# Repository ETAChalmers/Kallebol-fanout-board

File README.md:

# Kallebol-fanout-board
PCB to fan out and io expand the computers GPIO for the rotating Kallebol assembly

The GPIO of the kallebol computer was to slow for I2C. This board did not work and was replaced with a Raspberry Pi Pico instead.  

Features: 

* ~~UART for elevation control~~
* ~~I2C bus~~
* ~~I2C temp sensor~~
* ~~I2C 16 bit IO expander~~
* ~~Coax switch control~~
* ~~2x 12V outputs to drive LNB + 1.3 GHz LNA block.~~
* ~~PTT input to computer ... for future TX use.~~
* ~~12V -> 5V linear regulator, don't use this to power anything power hungry.~~
* ~~5V -> 3.3V linear regulator, don't use this to power anything power hungry.~~
* ~~2x Female RS232 ports (might need to be male in rev 2 ...)~~
* ~~Way too many resistors, all should not be mounted.~~
* ~~Way too many screw terminals~~
* ~~Chinesium (TM) voltmeter to monitor incoming 12V.~~

DC load: 
* Computer, 12V 5A peak 
* 10.5 GHz LNB, 12V ?A
* 1.3 GHz LNA, 12V ?A

Board2Pdf & jlcpcb plugin used in KiCad project.

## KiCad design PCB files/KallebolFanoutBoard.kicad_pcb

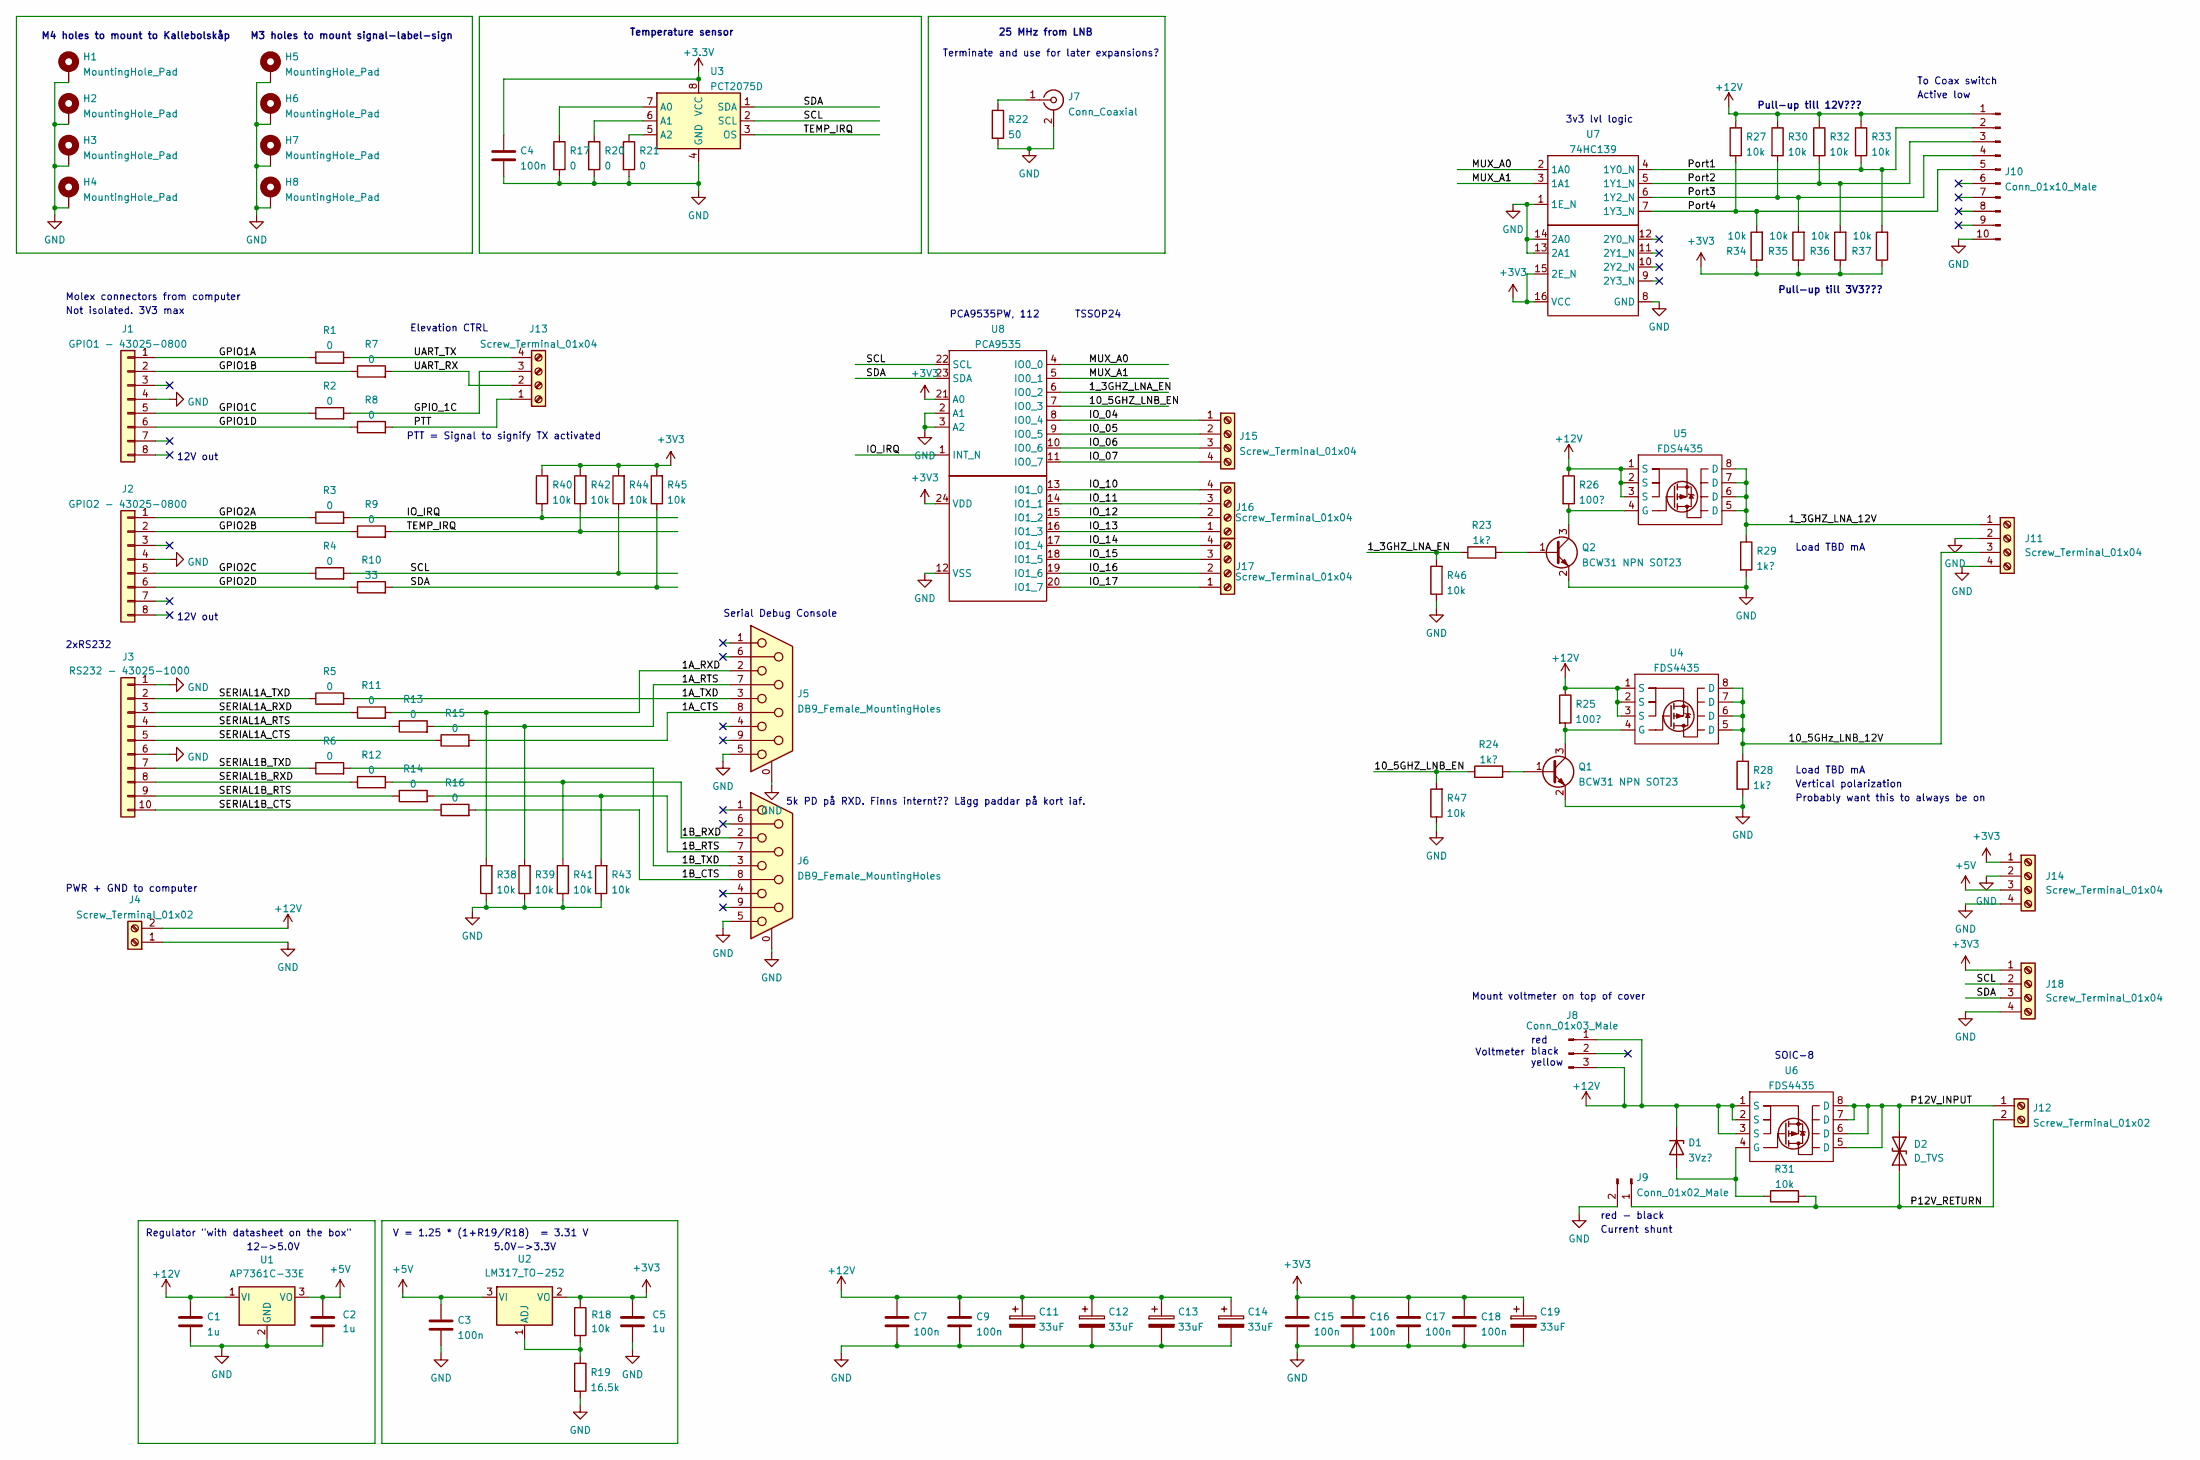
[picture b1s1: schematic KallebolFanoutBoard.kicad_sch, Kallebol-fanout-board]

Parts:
C1, C2, C5: 1u; C_0603_1608Metric_Pad1.08x0.95mm_HandSolder
C3, C4, C7, C9, C15, C16, C17, C18: 100n; C_0603_1608Metric_Pad1.08x0.95mm_HandSolder
C11, C12, C13, C14, C19: 33uF; CP_Elec_8x6.9
D1: 3Vz?; D_A-405_P7.62mm_Horizontal
D2: D_TVS; D_A-405_P7.62mm_Horizontal
H1, H2, H3, H4: MountingHole_Pad; MountingHole_4.3mm_M4_Pad_Via
H5, H6, H7, H8: MountingHole_Pad; MountingHole_3.2mm_M3_Pad_Via
J1: GPIO1 - 43025-0800; Molex_Micro-Fit_3.0_43045-0812_2x04_P3.00mm_Vertical
J2: GPIO2 - 43025-0800; Molex_Micro-Fit_3.0_43045-0812_2x04_P3.00mm_Vertical
J3: RS232 - 43025-1000; Molex_Micro-Fit_3.0_43045-1012_2x05_P3.00mm_Vertical
J4, J12: Screw_Terminal_01x02; TerminalBlock_Altech_AK300-2_P5.00mm
J5, J6: DB9_Female_MountingHoles; DSUB-9_Female_Vertical_P2.77x2.84mm_MountingHoles
J7: Conn_Coaxial; BNC_Amphenol_B6252HB-NPP3G-50_Horizontal
J8: Conn_01x03_Male; FanPinHeader_1x03_P2.54mm_Vertical
J9: Conn_01x02_Male; AMASS_XT30U-F_1x02_P5.0mm_Vertical
J10: Conn_01x10_Male; PinHeader_1x10_P2.54mm_Vertical
J11, J13, J14, J15, J16, J17, J18: Screw_Terminal_01x04; TerminalBlock_Altech_AK300-4_P5.00mm
Q1, Q2: BCW31 NPN SOT23; TSOT-23_HandSoldering
R1, R2, R3, R4, R5, R6, R7, R8, R9, R11, R12, R13, R14, R15, R16, R17, R20, R21: 0; R_0603_1608Metric_Pad0.98x0.95mm_HandSolder
R10: 33; R_0603_1608Metric_Pad0.98x0.95mm_HandSolder
R18, R27, R30, R31, R32, R33, R34, R35, R36, R37, R38, R39, R40, R41, R42, R43, R44, R45, R46, R47: 10k; R_0603_1608Metric_Pad0.98x0.95mm_HandSolder
R19: 16.5k; R_0603_1608Metric_Pad0.98x0.95mm_HandSolder
R22: 50; R_0603_1608Metric_Pad0.98x0.95mm_HandSolder
R23, R24, R28, R29: 1k?; R_0603_1608Metric_Pad0.98x0.95mm_HandSolder
R25, R26: 100?; R_0603_1608Metric_Pad0.98x0.95mm_HandSolder
U1: AP7361C-33E; SOT-223-3_TabPin2
U2: LM317_TO-252; TO-252-2
U3: PCT2075D; SO-8_3.9x4.9mm_P1.27mm
U4, U5, U6: FDS4435; SOIC-8_3.9x4.9mm_P1.27mm
U7: 74HC139; TSSOP-16_4.4x5mm_P0.65mm
U8: PCA9535; TSSOP-24_4.4x7.8mm_P0.65mm

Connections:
+5V: C2.1, C3.1, J14.3, U1.3 (VO), U2.3 (VI)
+12V: C1.1, C7.1, C9.1, C11.1, C12.1, C13.1, C14.1, D1.1 (K), J4.2, J8.1, J8.3, J10.1, R25.1, R26.1, R27.1, R30.1, R32.1, R33.1, U1.1 (VI), U4.1 (S), U4.2 (S), U4.3 (S), U5.1 (S), U5.2 (S), U5.3 (S), U6.1 (S), U6.2 (S), U6.3 (S)
/1A_CTS: J5.8, R15.2
/1A_RTS: J5.7, R13.2, R39.2
/1A_RXD: J5.2, R11.2, R38.2
/1A_TXD: J5.3, R5.2
/1B_CTS: J6.8, R16.2
/1B_RTS: J6.7, R14.2, R43.2
/1B_RXD: J6.2, R12.2, R41.2
/1B_TXD: J6.3, R6.2
/1_3GHZ_LNA_12V: J11.1, R29.1, U5.5 (D), U5.6 (D), U5.7 (D), U5.8 (D)
/1_3GHZ_LNA_EN: R23.1, R46.2, U8.6 (IO0_2)
/10_5GHZ_LNB_EN: R24.1, R47.2, U8.7 (IO0_3)
/10_5GHz_LNB_12V: J11.3, R28.1, U4.5 (D), U4.6 (D), U4.7 (D), U4.8 (D)
/GPIO1A: J1.1, R1.1
/GPIO1B: J1.2, R7.1
/GPIO1C: J1.5, R2.1
/GPIO1D: J1.6, R8.1
/GPIO2A: J2.1, R3.1
/GPIO2B: J2.2, R9.1
/GPIO2C: J2.5, R4.1
/GPIO2D: J2.6, R10.1
/GPIO_1C: J13.3, R2.2
/IO_04: J15.1, U8.8 (IO0_4)
/IO_05: J15.2, U8.9 (IO0_5)
/IO_06: J15.3, U8.10 (IO0_6)
/IO_07: J15.4, U8.11 (IO0_7)
/IO_10: J16.4, U8.13 (IO1_0)
/IO_11: J16.3, U8.14 (IO1_1)
/IO_12: J16.2, U8.15 (IO1_2)
/IO_13: J16.1, U8.16 (IO1_3)
/IO_14: J17.4, U8.17 (IO1_4)
/IO_15: J17.3, U8.18 (IO1_5)
/IO_16: J17.2, U8.19 (IO1_6)
/IO_17: J17.1, U8.20 (IO1_7)
/IO_IRQ: R3.2, R40.1, U8.1 (INT_N)
/MUX_A0: U7.2 (1A0), U8.4 (IO0_0)
/MUX_A1: U7.3 (1A1), U8.5 (IO0_1)
/P12V_INPUT: D2.2 (A2), J12.1, U6.5 (D), U6.6 (D), U6.7 (D), U6.8 (D)
/P12V_RETURN: D2.1 (A1), J9.1, J12.2, R31.2
/PTT: J13.1, R8.2
/Port1: J10.2, R33.2, R37.2, U7.4 (1Y0_N)
/Port2: J10.3, R32.2, R36.2, U7.5 (1Y1_N)
/Port3: J10.4, R30.2, R35.2, U7.6 (1Y2_N)
/Port4: J10.5, R27.2, R34.2, U7.7 (1Y3_N)
/SCL: J18.2, R4.2, R44.1, U3.2 (SCL), U8.22 (SCL)
/SDA: J18.3, R10.2, R45.1, U3.1 (SDA), U8.23 (SDA)
/SERIAL1A_CTS: J3.5, R15.1
/SERIAL1A_RTS: J3.4, R13.1
/SERIAL1A_RXD: J3.3, R11.1
/SERIAL1A_TXD: J3.2, R5.1
/SERIAL1B_CTS: J3.10, R16.1
/SERIAL1B_RTS: J3.9, R14.1
/SERIAL1B_RXD: J3.8, R12.1
/SERIAL1B_TXD: J3.7, R6.1
/TEMP_IRQ: R9.2, R42.1, U3.3 (OS)
/UART_RX: J13.2, R7.2
/UART_TX: J13.4, R1.2
GND: C1.2, C2.2, C3.2, C4.2, C5.2, C7.2, C9.2, C11.2, C12.2, C13.2, C14.2, C15.2, C16.2, C17.2, C18.2, C19.2, H1.1, H2.1, H3.1, H4.1, H5.1, H6.1, H7.1, H8.1, J1.4, J2.4, J3.1, J3.6, J4.1, J5.0 (PAD), J5.5, J6.0 (PAD), J6.5, J7.2 (Ext), J9.2, J10.10, J11.2, J11.4, J14.2, J14.4, J18.4, Q1.2 (E), Q2.2 (E), R17.2, R19.2, R20.2, R21.2, R22.2, R28.2, R29.2, R38.1, R39.1, R41.1, R43.1, R46.1, R47.1, U1.2 (GND), U3.4 (GND), U7.1 (1E_N), U7.8 (GND), U7.13 (2A1), U7.14 (2A0), U8.2 (A1), U8.3 (A2), U8.12 (VSS)
unnamed: D1.2 (A), R31.1, U6.4 (G)
unnamed: J7.1 (In), R22.1
unnamed: Q1.1 (B), R24.2
unnamed: Q1.3 (C), R25.2, U4.4 (G)
unnamed: Q2.1 (B), R23.2
unnamed: Q2.3 (C), R26.2, U5.4 (G)
unnamed: R17.1, U3.7 (A0)
unnamed: R18.2, R19.1, U2.1 (ADJ)
unnamed: R20.1, U3.6 (A1)
unnamed: R21.1, U3.5 (A2)

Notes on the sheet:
Not isolated. 3V3 max
M3 holes to mount signal-label-sign
Elevation CTRL
V = 1.25 * (1+R19/R18) = 3.31 V
Pull-up till 12V???
PCA9535PW, 112
red black yellow
SOIC-8
Voltmeter
Pull-up till 3V3???
Load TBD mA
5.0V->3.3V
Vertical polarization
2xRS232
TSSOP24
Serial Debug Console
M4 holes to mount to Kallebolskåp
Molex connectors from computer
Temperature sensor
Active low
red - black
12->5.0V
3v3 lvl logic
Mount voltmeter on top of cover
Current shunt
Probably want this to always be on
To Coax switch
5k PD på RXD. Finns internt?? Lägg paddar på kort iaf.
25 MHz from LNB
12V out
PTT = Signal to signify TX activated
PWR + GND to computer
Regulator "with datasheet on the box"
Terminate and use for later expansions?

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
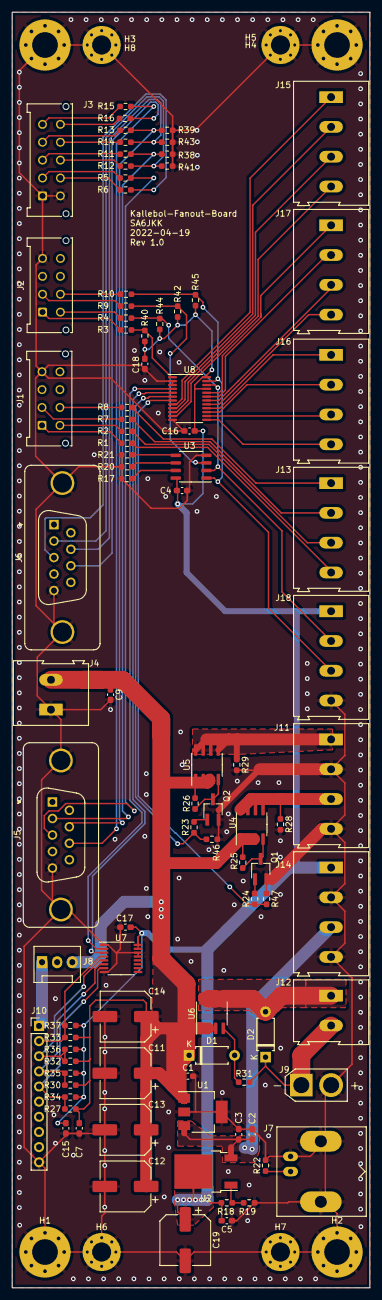
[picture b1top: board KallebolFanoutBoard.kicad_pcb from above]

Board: 2 copper layers, 60.0 x 214.0 mm, 101 parts (0 on the bottom side), 70 nets.

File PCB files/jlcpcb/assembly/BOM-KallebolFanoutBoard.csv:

Comment,Designator,Footprint,LCSC
0,R11,R_0603_1608Metric_Pad0.98x0.95mm_HandSolder,
10k,R41,R_0603_1608Metric_Pad0.98x0.95mm_HandSolder,
Screw_Terminal_01x02,J4,TerminalBlock_Altech_AK300-2_P5.00mm,
10k,R44,R_0603_1608Metric_Pad0.98x0.95mm_HandSolder,
1k?,R29,R_0603_1608Metric_Pad0.98x0.95mm_HandSolder,
100n,C17,C_0603_1608Metric_Pad1.08x0.95mm_HandSolder,
0,R16,R_0603_1608Metric_Pad0.98x0.95mm_HandSolder,
16.5k,R19,R_0603_1608Metric_Pad0.98x0.95mm_HandSolder,
0,R7,R_0603_1608Metric_Pad0.98x0.95mm_HandSolder,
10k,R40,R_0603_1608Metric_Pad0.98x0.95mm_HandSolder,
FDS4435,U6,SOIC-8_3.9x4.9mm_P1.27mm,
Screw_Terminal_01x04,J15,TerminalBlock_Altech_AK300-4_P5.00mm,
0,R14,R_0603_1608Metric_Pad0.98x0.95mm_HandSolder,
33uF,C12,CP_Elec_8x6.9,
FDS4435,U5,SOIC-8_3.9x4.9mm_P1.27mm,
Screw_Terminal_01x04,J16,TerminalBlock_Altech_AK300-4_P5.00mm,
33uF,C13,CP_Elec_8x6.9,
LM317_TO-252,U2,TO-252-2,
1k?,R28,R_0603_1608Metric_Pad0.98x0.95mm_HandSolder,
100?,R26,R_0603_1608Metric_Pad0.98x0.95mm_HandSolder,
33,R10,R_0603_1608Metric_Pad0.98x0.95mm_HandSolder,
1k?,R23,R_0603_1608Metric_Pad0.98x0.95mm_HandSolder,
MountingHole_Pad,H6,MountingHole_3.2mm_M3_Pad_Via,
100n,C7,C_0603_1608Metric_Pad1.08x0.95mm_HandSolder,
1k?,R24,R_0603_1608Metric_Pad0.98x0.95mm_HandSolder,
0,R9,R_0603_1608Metric_Pad0.98x0.95mm_HandSolder,
GPIO1 - 43025-0800,J1,Molex_Micro-Fit_3.0_43045-0812_2x04_P3.00mm_Vertical,
1u,C5,C_0603_1608Metric_Pad1.08x0.95mm_HandSolder,
10k,R31,R_0603_1608Metric_Pad0.98x0.95mm_HandSolder,
0,R17,R_0603_1608Metric_Pad0.98x0.95mm_HandSolder,
10k,R32,R_0603_1608Metric_Pad0.98x0.95mm_HandSolder,
MountingHole_Pad,H7,MountingHole_3.2mm_M3_Pad_Via,
MountingHole_Pad,H5,MountingHole_3.2mm_M3_Pad_Via,
100?,R25,R_0603_1608Metric_Pad0.98x0.95mm_HandSolder,
Conn_Coaxial,J7,BNC_Amphenol_B6252HB-NPP3G-50_Horizontal,
10k,R43,R_0603_1608Metric_Pad0.98x0.95mm_HandSolder,
AP7361C-33E,U1,SOT-223-3_TabPin2,
GPIO2 - 43025-0800,J2,Molex_Micro-Fit_3.0_43045-0812_2x04_P3.00mm_Vertical,
DB9_Female_MountingHoles,J5,DSUB-9_Female_Vertical_P2.77x2.84mm_MountingHoles,
Screw_Terminal_01x04,J14,TerminalBlock_Altech_AK300-4_P5.00mm,
Screw_Terminal_01x02,J12,TerminalBlock_Altech_AK300-2_P5.00mm,
10k,R39,R_0603_1608Metric_Pad0.98x0.95mm_HandSolder,
100n,C16,C_0603_1608Metric_Pad1.08x0.95mm_HandSolder,
FDS4435,U4,SOIC-8_3.9x4.9mm_P1.27mm,
Conn_01x10_Male,J10,PinHeader_1x10_P2.54mm_Vertical,
PCA9535,U8,TSSOP-24_4.4x7.8mm_P0.65mm,
100n,C3,C_0603_1608Metric_Pad1.08x0.95mm_HandSolder,
33uF,C14,CP_Elec_8x6.9,
1u,C1,C_0603_1608Metric_Pad1.08x0.95mm_HandSolder,
0,R4,R_0603_1608Metric_Pad0.98x0.95mm_HandSolder,
MountingHole_Pad,H1,MountingHole_4.3mm_M4_Pad_Via,
10k,R18,R_0603_1608Metric_Pad0.98x0.95mm_HandSolder,
74HC139,U7,TSSOP-16_4.4x5mm_P0.65mm,
MountingHole_Pad,H2,MountingHole_4.3mm_M4_Pad_Via,
100n,C4,C_0603_1608Metric_Pad1.08x0.95mm_HandSolder,
MountingHole_Pad,H3,MountingHole_4.3mm_M4_Pad_Via,
Screw_Terminal_01x04,J13,TerminalBlock_Altech_AK300-4_P5.00mm,
10k,R47,R_0603_1608Metric_Pad0.98x0.95mm_HandSolder,
100n,C15,C_0603_1608Metric_Pad1.08x0.95mm_HandSolder,
100n,C18,C_0603_1608Metric_Pad1.08x0.95mm_HandSolder,
100n,C9,C_0603_1608Metric_Pad1.08x0.95mm_HandSolder,
DB9_Female_MountingHoles,J6,DSUB-9_Female_Vertical_P2.77x2.84mm_MountingHoles,
3Vz?,D1,D_A-405_P7.62mm_Horizontal,
10k,R37,R_0603_1608Metric_Pad0.98x0.95mm_HandSolder,
33uF,C19,CP_Elec_8x6.9,
MountingHole_Pad,H8,MountingHole_3.2mm_M3_Pad_Via,
MountingHole_Pad,H4,MountingHole_4.3mm_M4_Pad_Via,
0,R21,R_0603_1608Metric_Pad0.98x0.95mm_HandSolder,
0,R2,R_0603_1608Metric_Pad0.98x0.95mm_HandSolder,
0,R8,R_0603_1608Metric_Pad0.98x0.95mm_HandSolder,
PCT2075D,U3,SO-8_3.9x4.9mm_P1.27mm,
0,R20,R_0603_1608Metric_Pad0.98x0.95mm_HandSolder,
D_TVS,D2,D_A-405_P7.62mm_Horizontal,
BCW31 NPN SOT23,Q2,TSOT-23_HandSoldering,
1u,C2,C_0603_1608Metric_Pad1.08x0.95mm_HandSolder,
Screw_Terminal_01x04,J17,TerminalBlock_Altech_AK300-4_P5.00mm,
0,R5,R_0603_1608Metric_Pad0.98x0.95mm_HandSolder,
BCW31 NPN SOT23,Q1,TSOT-23_HandSoldering,
Screw_Terminal_01x04,J11,TerminalBlock_Altech_AK300-4_P5.00mm,
10k,R38,R_0603_1608Metric_Pad0.98x0.95mm_HandSolder,
0,R15,R_0603_1608Metric_Pad0.98x0.95mm_HandSolder,
10k,R33,R_0603_1608Metric_Pad0.98x0.95mm_HandSolder,
0,R6,R_0603_1608Metric_Pad0.98x0.95mm_HandSolder,
0,R3,R_0603_1608Metric_Pad0.98x0.95mm_HandSolder,
10k,R36,R_0603_1608Metric_Pad0.98x0.95mm_HandSolder,
10k,R34,R_0603_1608Metric_Pad0.98x0.95mm_HandSolder,
10k,R45,R_0603_1608Metric_Pad0.98x0.95mm_HandSolder,
33uF,C11,CP_Elec_8x6.9,
RS232 - 43025-1000,J3,Molex_Micro-Fit_3.0_43045-1012_2x05_P3.00mm_Vertical,
0,R1,R_0603_1608Metric_Pad0.98x0.95mm_HandSolder,
0,R12,R_0603_1608Metric_Pad0.98x0.95mm_HandSolder,
10k,R42,R_0603_1608Metric_Pad0.98x0.95mm_HandSolder,
10k,R27,R_0603_1608Metric_Pad0.98x0.95mm_HandSolder,
10k,R30,R_0603_1608Metric_Pad0.98x0.95mm_HandSolder,
Conn_01x03_Male,J8,FanPinHeader_1x03_P2.54mm_Vertical,
10k,R35,R_0603_1608Metric_Pad0.98x0.95mm_HandSolder,
50,R22,R_0603_1608Metric_Pad0.98x0.95mm_HandSolder,
Conn_01x02_Male,J9,AMASS_XT30U-F_1x02_P5.0mm_Vertical,
Screw_Terminal_01x04,J18,TerminalBlock_Altech_AK300-4_P5.00mm,
0,R13,R_0603_1608Metric_Pad0.98x0.95mm_HandSolder,
10k,R46,R_0603_1608Metric_Pad0.98x0.95mm_HandSolder,

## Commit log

2022-05-26 Adds the PCB files for rev 1
2022-05-26 Documentation is fun.
2022-10-22 Update readme before archiving.
2022-10-22 Update readme again ...
